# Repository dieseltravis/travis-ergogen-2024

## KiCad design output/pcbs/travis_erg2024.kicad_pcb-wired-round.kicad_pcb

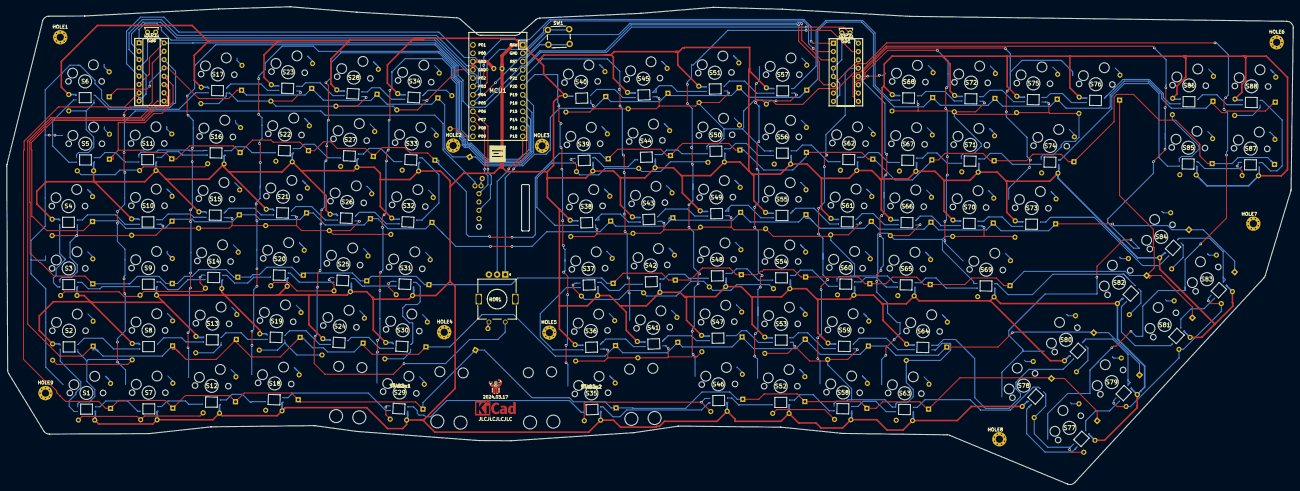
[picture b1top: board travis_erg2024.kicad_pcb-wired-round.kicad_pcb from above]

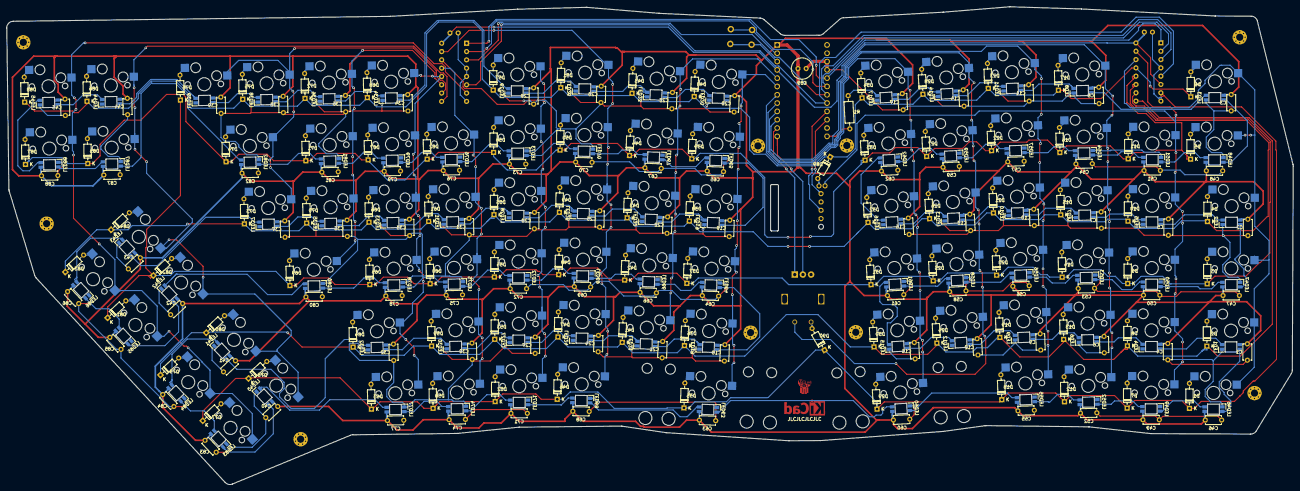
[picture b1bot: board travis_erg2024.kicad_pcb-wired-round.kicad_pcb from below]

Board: 2 copper layers, 393.3 x 146.1 mm, 379 parts (268 on the bottom side), 210 nets.

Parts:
C1, C2, C3, C4, C5, C6, C7, C8, C9, C10, C11, C12, C13, C14, C15, C16, C17, C18, C19, C20, C21, C22, C23, C24, C25, C26, C27, C28, C29, C30, C31, C32, C33, C34, C35, C36, C37, C38, C39, C40, C41, C42, C43, C44, C45, C46, C47, C48, C49, C50, C51, C52, C53, C54, C55, C56, C57, C58, C59, C60, C61, C62, C63, C64, C65, C66, C67, C68, C69, C70, C71, C72, C73, C74, C75, C76, C77, C78, C79, C80, C81, C82, C83, C84, C85, C86, C87, C88: C_Disc_D4.7mm_W2.5mm_P5.00mm
C89: C_Radial_D6.3mm_H11.0mm_P2.50mm
C90, C91: C_Disc_D3.8mm_W2.6mm_P2.50mm
D1, D2, D3, D4, D5, D6, D7, D8, D9, D10, D11, D12, D13, D14, D15, D16, D17, D18, D19, D20, D21, D22, D23, D24, D25, D26, D27, D28, D29, D30, D31, D32, D33, D34, D35, D36, D37, D38, D39, D40, D41, D42, D43, D44, D45, D46, D47, D48, D49, D50, D51, D52, D53, D54, D55, D56, D57, D58, D59, D60, D61, D62, D63, D64, D65, D66, D67, D68, D69, D70, D71, D72, D73, D74, D75, D76, D77, D78, D79, D80, D81, D82, D83, D84, D85, D86, D87, D88, D89, D90: 1N4148; Diode_DO-35
DIP1, DIP2: DIP-16_W7.62mm_Socket
HOLE1, HOLE2, HOLE3, HOLE4, HOLE5, HOLE6, HOLE7, HOLE8, HOLE9: MountingHole_2.2mm_M2_Pad_Via
LED1, LED2, LED3, LED4, LED5, LED6, LED7, LED8, LED9, LED10, LED11, LED12, LED13, LED14, LED15, LED16, LED17, LED18, LED19, LED20, LED21, LED22, LED23, LED24, LED25, LED26, LED27, LED28, LED29, LED30, LED31, LED32, LED33, LED34, LED35, LED36, LED37, LED38, LED39, LED40, LED41, LED42, LED43, LED44, LED45, LED46, LED47, LED48, LED49, LED50, LED51, LED52, LED53, LED54, LED55, LED56, LED57, LED58, LED59, LED60, LED61, LED62, LED63, LED64, LED65, LED66, LED67, LED68, LED69, LED70, LED71, LED72, LED73, LED74, LED75, LED76, LED77, LED78, LED79, LED80, LED81, LED82, LED83, LED84, LED85, LED86, LED87, LED88: led_SK6812mini-e (per-keysingle-side)
LOGO1: ergogen
LOGO2: travis
MCU1: ProMicro
R1: R_Axial_DIN0207_L6.3mm_D2.5mm_P10.16mm_Horizontal
ROT1: rotary_encoder
S1, S2, S3, S4, S5, S6, S7, S8, S9, S10, S11, S12, S13, S14, S15, S16, S17, S18, S19, S20, S21, S22, S23, S24, S25, S26, S27, S28, S29, S30, S31, S32, S33, S34, S35, S36, S37, S38, S39, S40, S41, S42, S43, S44, S45, S46, S47, S48, S49, S50, S51, S52, S53, S54, S55, S56, S57, S58, S59, S60, S61, S62, S63, S64, S65, S66, S67, S68, S69, S70, S71, S72, S73, S74, S75, S76, S77, S78, S79, S80, S81, S82, S83, S84, S85, S86, S87, S88: MX
STAB2u1, STAB2u2: Stabilizer_MX_2.00u
STAB3u1, STAB3u2: Stabilizer_MX_3.00u
SW1: SW_PUSH_6mm_H4.3mm
SYM1: KiCad-Logo_5mm_Copper

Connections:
GND: C1.2, C2.2, C3.2, C4.2, C5.2, C6.2, C7.2, C8.2, C9.2, C10.2, C11.2, C12.2, C13.2, C14.2, C15.2, C16.2, C17.2, C18.2, C19.2, C20.2, C21.2, C22.2, C23.2, C24.2, C25.2, C26.2, C27.2, C28.2, C29.2, C30.2, C31.2, C32.2, C33.2, C34.2, C35.2, C36.2, C37.2, C38.2, C39.2, C40.2, C41.2, C42.2, C43.2, C44.2, C45.2, C46.2, C47.2, C48.2, C49.2, C50.2, C51.2, C52.2, C53.2, C54.2, C55.2, C56.2, C57.2, C58.2, C59.2, C60.2, C61.2, C62.2, C63.2, C64.2, C65.2, C66.2, C67.2, C68.2, C69.2, C70.2, C71.2, C72.2, C73.2, C74.2, C75.2, C76.2, C77.2, C78.2, C79.2, C80.2, C81.2, C82.2, C83.2, C84.2, C85.2, C86.2, C87.2, C88.2, C89.2, C90.2, C91.2, DIP1.4, DIP1.8, DIP2.4, DIP2.5, DIP2.8, LED1.3, LED2.3, LED3.3, LED4.3, LED5.3, LED6.3, LED7.3, LED8.3, LED9.3, LED10.3, LED11.3, LED12.3, LED13.3, LED14.3, LED15.3, LED16.3, LED17.3, LED18.3, LED19.3, LED20.3, LED21.3, LED22.3, LED23.3, LED24.3, LED25.3, LED26.3, LED27.3, LED28.3, LED29.3, LED30.3, LED31.3, LED32.3, LED33.3, LED34.3, LED35.3, LED36.3, LED37.3, LED38.3, LED39.3, LED40.3, LED41.3, LED42.3, LED43.3, LED44.3, LED45.3, LED46.3, LED47.3, LED48.3, LED49.3, LED50.3, LED51.3, LED52.3, LED53.3, LED54.3, LED55.3, LED56.3, LED57.3, LED58.3, LED59.3, LED60.3, LED61.3, LED62.3, LED63.3, LED64.3, LED65.3, LED66.3, LED67.3, LED68.3, LED69.3, LED70.3, LED71.3, LED72.3, LED73.3, LED74.3, LED75.3, LED76.3, LED77.3, LED78.3, LED79.3, LED80.3, LED81.3, LED82.3, LED83.3, LED84.3, LED85.3, LED86.3, LED87.3, LED88.3, MCU1.2, MCU1.15, MCU1.16, ROT1.B, SW1.1
LED: MCU1.24, R1.1
LED_0: LED17.4, R1.2
LED_1: LED14.4, LED17.2
LED_2: LED11.4, LED14.2
LED_3: LED8.4, LED11.2
LED_4: LED3.4, LED8.2
LED_5: LED3.2, LED48.4
LED_6: LED48.2, LED51.4
LED_7: LED51.2, LED54.4
LED_8: LED54.2, LED57.4
LED_9: LED57.2, LED59.4
LED_10: LED59.2, LED62.4
LED_11: LED16.4, LED62.2
LED_12: LED13.4, LED16.2
LED_13: LED10.4, LED13.2
LED_14: LED7.4, LED10.2
LED_15: LED5.4, LED7.2
LED_16: LED2.4, LED5.2
LED_17: LED2.2, LED47.4
LED_18: LED47.2, LED50.4
LED_19: LED50.2, LED53.4
LED_20: LED53.2, LED56.4
LED_21: LED56.2, LED58.4
LED_22: LED58.2, LED61.4
LED_23: LED15.4, LED61.2
LED_24: LED12.4, LED15.2
LED_25: LED9.4, LED12.2
LED_26: LED6.4, LED9.2
LED_27: LED4.4, LED6.2
LED_28: LED1.4, LED4.2
LED_29: LED1.2, LED46.4
LED_30: LED46.2, LED49.4
LED_31: LED49.2, LED52.4
LED_32: LED52.2, LED55.4
LED_33: LED55.2, LED60.4
LED_34: LED60.2, LED63.4
LED_35: LED63.2, LED68.4
LED_36: LED68.2, LED71.4
LED_37: LED71.2, LED74.4
LED_38: LED74.2, LED77.4
LED_39: LED40.4, LED77.2
LED_40: LED40.2, LED83.4
LED_41: LED83.2, LED84.4
LED_42: LED41.4, LED84.2
LED_43: LED32.4, LED41.2
LED_44: LED30.4, LED32.2
LED_45: LED27.4, LED30.2
LED_46: LED24.4, LED27.2
LED_47: LED21.4, LED24.2
LED_48: LED18.4, LED21.2
LED_49: LED18.2, LED64.4
LED_50: LED64.2, LED66.4
LED_51: LED66.2, LED69.4
LED_52: LED69.2, LED72.4
LED_53: LED72.2, LED75.4
LED_54: LED75.2, LED78.4
LED_55: LED78.2, LED80.4
LED_56: LED42.4, LED80.2
LED_57: LED42.2, LED85.4
LED_58: LED85.2, LED86.4
LED_59: LED43.4, LED86.2
LED_60: LED37.4, LED43.2
LED_61: LED35.4, LED37.2
LED_62: LED33.4, LED35.2
LED_63: LED31.4, LED33.2
LED_64: LED28.4, LED31.2
LED_65: LED25.4, LED28.2
LED_66: LED22.4, LED25.2
LED_67: LED19.4, LED22.2
LED_68: LED19.2, LED65.4
LED_69: LED65.2, LED67.4
LED_70: LED67.2, LED70.4
LED_71: LED70.2, LED73.4
LED_72: LED73.2, LED76.4
LED_73: LED76.2, LED79.4
LED_74: LED79.2, LED81.4
LED_75: LED81.2, LED82.4
LED_76: LED82.2, LED87.4
LED_77: LED87.2, LED88.4
LED_78: LED45.4, LED88.2
LED_79: LED44.4, LED45.2
LED_80: LED39.4, LED44.2
LED_81: LED38.4, LED39.2
LED_82: LED36.4, LED38.2
LED_83: LED34.4, LED36.2
LED_84: LED29.4, LED34.2
LED_85: LED26.4, LED29.2
LED_86: LED23.4, LED26.2
LED_87: LED20.4, LED23.2
RAW: C1.1, C2.1, C3.1, C4.1, C5.1, C6.1, C7.1, C8.1, C9.1, C10.1, C11.1, C12.1, C13.1, C14.1, C15.1, C16.1, C17.1, C18.1, C19.1, C20.1, C21.1, C22.1, C23.1, C24.1, C25.1, C26.1, C27.1, C28.1, C29.1, C30.1, C31.1, C32.1, C33.1, C34.1, C35.1, C36.1, C37.1, C38.1, C39.1, C40.1, C41.1, C42.1, C43.1, C44.1, C45.1, C46.1, C47.1, C48.1, C49.1, C50.1, C51.1, C52.1, C53.1, C54.1, C55.1, C56.1, C57.1, C58.1, C59.1, C60.1, C61.1, C62.1, C63.1, C64.1, C65.1, C66.1, C67.1, C68.1, C69.1, C70.1, C71.1, C72.1, C73.1, C74.1, C75.1, C76.1, C77.1, C78.1, C79.1, C80.1, C81.1, C82.1, C83.1, C84.1, C85.1, C86.1, C87.1, C88.1, C89.1, LED1.1, LED2.1, LED3.1, LED4.1, LED5.1, LED6.1, LED7.1, LED8.1, LED9.1, LED10.1, LED11.1, LED12.1, LED13.1, LED14.1, LED15.1, LED16.1, LED17.1, LED18.1, LED19.1, LED20.1, LED21.1, LED22.1, LED23.1, LED24.1, LED25.1, LED26.1, LED27.1, LED28.1, LED29.1, LED30.1, LED31.1, LED32.1, LED33.1, LED34.1, LED35.1, LED36.1, LED37.1, LED38.1, LED39.1, LED40.1, LED41.1, LED42.1, LED43.1, LED44.1, LED45.1, LED46.1, LED47.1, LED48.1, LED49.1, LED50.1, LED51.1, LED52.1, LED53.1, LED54.1, LED55.1, LED56.1, LED57.1, LED58.1, LED59.1, LED60.1, LED61.1, LED62.1, LED63.1, LED64.1, LED65.1, LED66.1, LED67.1, LED68.1, LED69.1, LED70.1, LED71.1, LED72.1, LED73.1, LED74.1, LED75.1, LED76.1, LED77.1, LED78.1, LED79.1, LED80.1, LED81.1, LED82.1, LED83.1, LED84.1, LED85.1, LED86.1, LED87.1, LED88.1, MCU1.1
RST: MCU1.3, SW1.2
VCC: C90.1, C91.1, DIP1.6, DIP1.16, DIP2.16, MCU1.4
arrows_left_bottom: D77.2, S77.2
arrows_left_top: D78.2, S78.2
arrows_right_bottom: D79.2, S79.2
arrows_right_top: D80.2, S80.2
col0: DIP1.14, S1.1, S2.1, S3.1, S4.1, S5.1, S6.1
col1: DIP1.15, S7.1, S8.1, S9.1, S10.1, S11.1
col2: MCU1.10, S12.1, S13.1, S14.1, S15.1, S16.1, S17.1
col3: MCU1.9, S18.1, S19.1, S20.1, S21.1, S22.1, S23.1
col4: MCU1.8, ROT1.1, S24.1, S25.1, S26.1, S27.1, S28.1
col5: MCU1.7, S29.1, S30.1, S31.1, S32.1, S33.1, S34.1
col6: MCU1.6, S35.1, S36.1, S37.1, S38.1, S39.1, S40.1
col7: MCU1.5, S41.1, S42.1, S43.1, S44.1, S45.1
col8: DIP2.15, S46.1, S47.1, S48.1, S49.1, S50.1, S51.1
col9: DIP2.14, S52.1, S53.1, S54.1, S55.1, S56.1, S57.1
col10: DIP2.13, S58.1, S59.1, S60.1, S61.1, S62.1
col11: DIP2.12, S63.1, S64.1, S65.1, S66.1, S67.1, S68.1
col12: DIP2.11, S69.1, S70.1, S71.1, S72.1
col13: DIP2.10, S73.1, S74.1, S75.1, S76.1
col14: DIP2.9, S78.1, S80.1, S82.1, S84.1, S85.1, S86.1
col15: DIP2.7, S77.1, S79.1, S81.1, S83.1, S87.1, S88.1
encA: MCU1.11, ROT1.A
encC: MCU1.12, ROT1.C
enc_to: D90.2, ROT1.2
matrixl_index_bottom: D24.2, S24.2
matrixl_index_func: D28.2, S28.2
matrixl_index_home: D25.2, S25.2
matrixl_index_num: D27.2, S27.2
matrixl_index_top: D26.2, S26.2
matrixl_inner_bottom: D30.2, S30.2
matrixl_inner_func: D34.2, S34.2
matrixl_inner_home: D31.2, S31.2
matrixl_inner_mod: D29.2, S29.2
matrixl_inner_num: D33.2, S33.2
matrixl_inner_top: D32.2, S32.2
matrixl_middle_bottom: D19.2, S19.2
matrixl_middle_func: D23.2, S23.2
matrixl_middle_home: D20.2, S20.2
matrixl_middle_mod: D18.2, S18.2
matrixl_middle_num: D22.2, S22.2
matrixl_middle_top: D21.2, S21.2
matrixl_outer_bottom: D2.2, S2.2
matrixl_outer_func: D6.2, S6.2
matrixl_outer_home: D3.2, S3.2
matrixl_outer_mod: D1.2, S1.2
matrixl_outer_num: D5.2, S5.2
matrixl_outer_top: D4.2, S4.2
matrixl_pinky_bottom: D8.2, S8.2
matrixl_pinky_home: D9.2, S9.2
matrixl_pinky_mod: D7.2, S7.2
matrixl_pinky_num: D11.2, S11.2
matrixl_pinky_top: D10.2, S10.2
matrixl_ring_bottom: D13.2, S13.2
matrixl_ring_func: D17.2, S17.2
matrixl_ring_home: D14.2, S14.2
matrixl_ring_mod: D12.2, S12.2
matrixl_ring_num: D16.2, S16.2
matrixl_ring_top: D15.2, S15.2
matrixr_index_bottom: D41.2, S41.2
matrixr_index_func: D45.2, S45.2
matrixr_index_home: D42.2, S42.2
matrixr_index_num: D44.2, S44.2
matrixr_index_top: D43.2, S43.2
matrixr_inner_bottom: D36.2, S36.2
matrixr_inner_func: D40.2, S40.2
matrixr_inner_home: D37.2, S37.2
matrixr_inner_mod: D35.2, S35.2
matrixr_inner_num: D39.2, S39.2
matrixr_inner_top: D38.2, S38.2
matrixr_middle_bottom: D47.2, S47.2
matrixr_middle_func: D51.2, S51.2
matrixr_middle_home: D48.2, S48.2
matrixr_middle_mod: D46.2, S46.2
matrixr_middle_num: D50.2, S50.2
matrixr_middle_top: D49.2, S49.2
matrixr_outer2_func: D72.2, S72.2
matrixr_outer2_home: D69.2, S69.2
matrixr_outer2_num: D71.2, S71.2
matrixr_outer2_top: D70.2, S70.2
matrixr_outer3_func: D75.2, S75.2
matrixr_outer3_num: D74.2, S74.2
matrixr_outer3_top: D73.2, S73.2
matrixr_outer4_func: D76.2, S76.2
matrixr_outer_bottom: D64.2, S64.2
matrixr_outer_func: D68.2, S68.2
matrixr_outer_home: D65.2, S65.2
matrixr_outer_mod: D63.2, S63.2
matrixr_outer_num: D67.2, S67.2
matrixr_outer_top: D66.2, S66.2
matrixr_pinky_bottom: D59.2, S59.2
matrixr_pinky_home: D60.2, S60.2
matrixr_pinky_mod: D58.2, S58.2
matrixr_pinky_num: D62.2, S62.2
matrixr_pinky_top: D61.2, S61.2
matrixr_ring_bottom: D53.2, S53.2
matrixr_ring_func: D57.2, S57.2
matrixr_ring_home: D54.2, S54.2
matrixr_ring_mod: D52.2, S52.2
matrixr_ring_num: D56.2, S56.2
matrixr_ring_top: D55.2, S55.2
mux0: DIP1.1, DIP2.1, MCU1.17
mux1: DIP1.2, DIP2.2, MCU1.18
mux2: DIP1.3, DIP2.3, MCU1.19
mux3: DIP1.5, DIP2.6, MCU1.20
pages_left_bottom: D81.2, S81.2
pages_left_top: D82.2, S82.2
pages_right_bottom: D83.2, S83.2
pages_right_top: D84.2, S84.2
row0: D6.1, D17.1, D23.1, D28.1, D34.1, D40.1, D45.1, D51.1, D57.1, D68.1, D72.1, D75.1, D86.1, D88.1, D89.1, DIP1.13
row1: D5.1, D11.1, D16.1, D22.1, D27.1, D33.1, D39.1, D44.1, D50.1, D56.1, D62.1, D67.1, D71.1, D74.1, D85.1, D87.1, DIP1.12
row2: D4.1, D10.1, D15.1, D21.1, D26.1, D32.1, D38.1, D43.1, D49.1, D55.1, D61.1, D66.1, D70.1, D73.1, D83.1, D84.1, DIP1.11
row3: D3.1, D9.1, D14.1, D20.1, D25.1, D31.1, D37.1, D42.1, D48.1, D54.1, D60.1, D65.1, D69.1, D76.1, D81.1, D82.1, DIP1.10
row4: D2.1, D8.1, D13.1, D19.1, D24.1, D30.1, D36.1, D41.1, D47.1, D53.1, D59.1, D64.1, D79.1, D80.1, DIP1.9
row5: D1.1, D7.1, D12.1, D18.1, D29.1, D35.1, D46.1, D52.1, D58.1, D63.1, D77.1, D78.1, D90.1, DIP1.7
special_left_bottom: D85.2, S85.2
special_left_top: D86.2, S86.2
special_right_bottom: D87.2, S87.2
special_right_top: D88.2, S88.2

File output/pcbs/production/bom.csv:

Designator,Footprint,Quantity,Value,LCSC Part #
C1,C_Radial_D6.3mm_H11.0mm_P2.50mm,1,C_Radial_D6.3mm_H11.0mm_P2.50mm,
"C2, C3",C_Disc_D3.8mm_W2.6mm_P2.50mm,2,C_Disc_D3.8mm_W2.6mm_P2.50mm,
"D1, D2, KD1, KD10, KD11, KD12, KD13, KD14, KD15, KD16, KD17, KD18, KD19, KD2, KD20, KD21, KD22, KD23, KD24, KD25, KD26, KD27, KD28, KD29, KD3, KD30, KD31, KD32, KD33, KD34, KD35, KD36, KD37, KD38, KD39, KD4, KD40, KD41, KD42, KD43, KD44, KD45, KD46, KD47, KD48, KD49, KD5, KD50, KD51, KD52, KD53, KD54, KD55, KD56, KD57, KD58, KD59, KD6, KD60, KD61, KD62, KD63, KD64, KD65, KD66, KD67, KD68, KD69, KD7, KD70, KD71, KD72, KD73, KD74, KD75, KD76, KD77, KD78, KD79, KD8, KD80, KD81, KD82, KD83, KD84, KD85, KD86, KD87, KD88, KD9",Diode_DO-35,90,1N4148,
"DIP1, DIP2",DIP-16_W7.62mm_Socket,2,DIP-16_W7.62mm_Socket,
"HOLE1, HOLE2, HOLE3, HOLE4, HOLE5, HOLE6, HOLE7, HOLE8, HOLE9",MountingHole_2.2mm_M2_Pad_Via,9,,
"KC1, KC10, KC11, KC12, KC13, KC14, KC15, KC16, KC17, KC18, KC19, KC2, KC20, KC21, KC22, KC23, KC24, KC25, KC26, KC27, KC28, KC29, KC3, KC30, KC31, KC32, KC33, KC34, KC35, KC36, KC37, KC38, KC39, KC4, KC40, KC41, KC42, KC43, KC44, KC45, KC46, KC47, KC48, KC49, KC5, KC50, KC51, KC52, KC53, KC54, KC55, KC56, KC57, KC58, KC59, KC6, KC60, KC61, KC62, KC63, KC64, KC65, KC66, KC67, KC68, KC69, KC7, KC70, KC71, KC72, KC73, KC74, KC75, KC76, KC77, KC78, KC79, KC8, KC80, KC81, KC82, KC83, KC84, KC85, KC86, KC87, KC88, KC9",C_Disc_D4.7mm_W2.5mm_P5.00mm,88,104,
"KLED1, KLED10, KLED11, KLED12, KLED13, KLED14, KLED15, KLED16, KLED17, KLED18, KLED19, KLED2, KLED20, KLED21, KLED22, KLED23, KLED24, KLED25, KLED26, KLED27, KLED28, KLED29, KLED3, KLED30, KLED31, KLED32, KLED33, KLED34, KLED35, KLED36, KLED37, KLED38, KLED39, KLED4, KLED40, KLED41, KLED42, KLED43, KLED44, KLED45, KLED46, KLED47, KLED48, KLED49, KLED5, KLED50, KLED51, KLED52, KLED53, KLED54, KLED55, KLED56, KLED57, KLED58, KLED59, KLED6, KLED60, KLED61, KLED62, KLED63, KLED64, KLED65, KLED66, KLED67, KLED68, KLED69, KLED7, KLED70, KLED71, KLED72, KLED73, KLED74, KLED75, KLED76, KLED77, KLED78, KLED79, KLED8, KLED80, KLED81, KLED82, KLED83, KLED84, KLED85, KLED86, KLED87, KLED88, KLED9",led_SK6812mini-e (per-key single-side),88,SK6812mini-e,
"KSW1, KSW10, KSW11, KSW12, KSW13, KSW14, KSW15, KSW16, KSW17, KSW18, KSW19, KSW2, KSW20, KSW21, KSW22, KSW23, KSW24, KSW25, KSW26, KSW27, KSW28, KSW29, KSW3, KSW30, KSW31, KSW32, KSW33, KSW34, KSW35, KSW36, KSW37, KSW38, KSW39, KSW4, KSW40, KSW41, KSW42, KSW43, KSW44, KSW45, KSW46, KSW47, KSW48, KSW49, KSW5, KSW50, KSW51, KSW52, KSW53, KSW54, KSW55, KSW56, KSW57, KSW58, KSW59, KSW6, KSW60, KSW61, KSW62, KSW63, KSW64, KSW65, KSW66, KSW67, KSW68, KSW69, KSW7, KSW70, KSW71, KSW72, KSW73, KSW74, KSW75, KSW76, KSW77, KSW78, KSW79, KSW8, KSW80, KSW81, KSW82, KSW83, KSW84, KSW85, KSW86, KSW87, KSW88, KSW9",MX,88,Kailh MX Switch Sockets,
MCU1,ProMicro,1,,
R1,R_Axial_DIN0207_L6.3mm_D2.5mm_P10.16mm_Horizontal,1,R_Axial_DIN0207_L6.3mm_D2.5mm_P10.16mm_Horizontal,
ROT1,rotary_encoder,1,,
SW1,SW_PUSH_6mm_H4.3mm,1,SW_PUSH_6mm_H4.3mm,

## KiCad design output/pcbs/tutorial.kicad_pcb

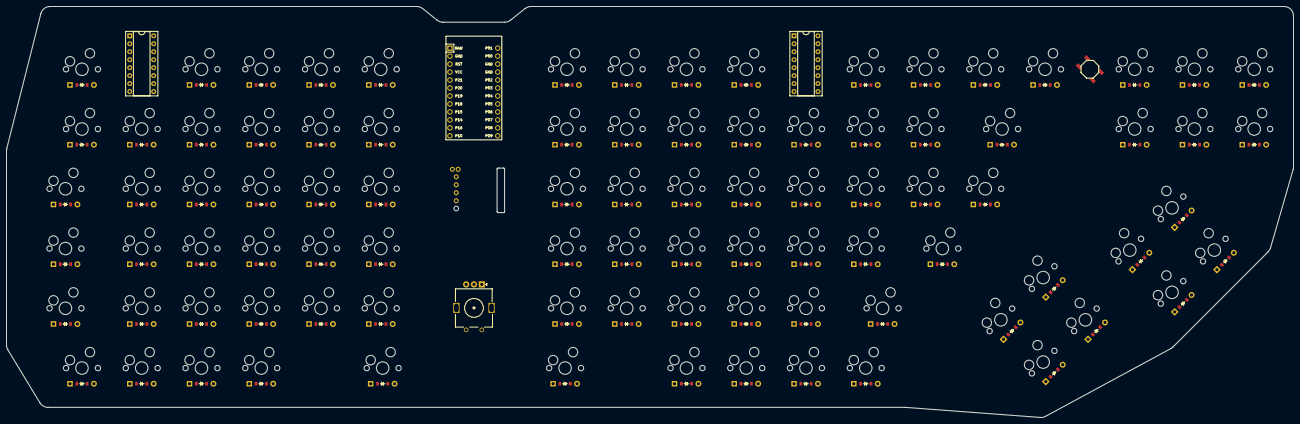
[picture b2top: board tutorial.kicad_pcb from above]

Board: 2 copper layers, 410.2 x 131.0 mm, 185 parts (0 on the bottom side), 52 nets, no tracks yet.

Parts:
B1: SW_TACT_ALPS_SKQGABE010
D1, D2, D3, D4, D5, D6, D7, D8, D9, D10, D11, D12, D13, D14, D15, D16, D17, D18, D19, D20, D21, D22, D23, D24, D25, D26, D27, D28, D29, D30, D31, D32, D33, D34, D35, D36, D37, D38, D39, D40, D41, D42, D43, D44, D45, D46, D47, D48, D49, D50, D51, D52, D53, D54, D55, D56, D57, D58, D59, D60, D61, D62, D63, D64, D65, D66, D67, D68, D69, D70, D71, D72, D73, D74, D75, D76, D77, D78, D79, D80, D81, D82, D83, D84, D85, D86, D87, D88, D89, D90: ComboDiode
DIP1, DIP2: DIP-16_W7.62mm_Socket
MCU1: ProMicro
ROT1: rotary_encoder
S1, S2, S3, S4, S5, S6, S7, S8, S9, S10, S11, S12, S13, S14, S15, S16, S17, S18, S19, S20, S21, S22, S23, S24, S25, S26, S27, S28, S29, S30, S31, S32, S33, S34, S35, S36, S37, S38, S39, S40, S41, S42, S43, S44, S45, S46, S47, S48, S49, S50, S51, S52, S53, S54, S55, S56, S57, S58, S59, S60, S61, S62, S63, S64, S65, S66, S67, S68, S69, S70, S71, S72, S73, S74, S75, S76, S77, S78, S79, S80, S81, S82, S83, S84, S85, S86, S87, S88, S89, S90: MX

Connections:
GND: B1.1, DIP1.1, DIP1.2, DIP1.3, DIP1.4, DIP1.5, DIP1.6, DIP1.7, DIP1.8, DIP1.9, DIP1.10, DIP1.11, DIP1.12, DIP1.13, DIP1.14, DIP1.15, DIP2.1, DIP2.2, DIP2.3, DIP2.4, DIP2.5, DIP2.6, DIP2.7, DIP2.8, DIP2.9, DIP2.10, DIP2.11, DIP2.12, DIP2.13, DIP2.14, DIP2.15, MCU1.2, MCU1.15, MCU1.16, ROT1.1, ROT1.2, ROT1.A, ROT1.B, ROT1.C
RST: B1.2, MCU1.3
VCC: DIP1.16, DIP2.16, MCU1.4
index_bottom: D25.2, D41.2, S25.2, S41.2
index_func: D29.2, D45.2, S29.2, S45.2
index_home: D26.2, D42.2, S26.2, S42.2
index_mod: D24.2, S24.2
index_num: D28.2, D44.2, S28.2, S44.2
index_top: D27.2, D43.2, S27.2, S43.2
inner_bottom: D30.2, D36.2, S30.2, S36.2
inner_func: D34.2, D40.2, S34.2, S40.2
inner_home: D31.2, D37.2, S31.2, S37.2
inner_mod: D35.2, S35.2
inner_num: D33.2, D39.2, S33.2, S39.2
inner_top: D32.2, D38.2, S32.2, S38.2
left_bottom: D77.2, D81.2, D85.2, S77.2, S81.2, S85.2
left_top: D78.2, D82.2, D86.2, S78.2, S82.2, S86.2
mid_bottom: D87.2, S87.2
mid_top: D88.2, S88.2
middle_bottom: D19.2, D47.2, S19.2, S47.2
middle_func: D23.2, D51.2, S23.2, S51.2
middle_home: D20.2, D48.2, S20.2, S48.2
middle_mod: D18.2, D46.2, S18.2, S46.2
middle_num: D22.2, D50.2, S22.2, S50.2
middle_top: D21.2, D49.2, S21.2, S49.2
outer2_func: D72.2, S72.2
outer2_home: D69.2, S69.2
outer2_num: D71.2, S71.2
outer2_top: D70.2, S70.2
outer3_func: D75.2, S75.2
outer3_num: D74.2, S74.2
outer3_top: D73.2, S73.2
outer4_func: D76.2, S76.2
outer_bottom: D2.2, D64.2, S2.2, S64.2
outer_func: D6.2, D68.2, S6.2, S68.2
outer_home: D3.2, D65.2, S3.2, S65.2
outer_mod: D1.2, D63.2, S1.2, S63.2
outer_num: D5.2, D67.2, S5.2, S67.2
outer_top: D4.2, D66.2, S4.2, S66.2
pinky_bottom: D8.2, D59.2, S8.2, S59.2
pinky_home: D9.2, D60.2, S9.2, S60.2
pinky_mod: D7.2, D58.2, S7.2, S58.2
pinky_num: D11.2, D62.2, S11.2, S62.2
pinky_top: D10.2, D61.2, S10.2, S61.2
right_bottom: D79.2, D83.2, D89.2, S79.2, S83.2, S89.2
right_top: D80.2, D84.2, D90.2, S80.2, S84.2, S90.2
ring_bottom: D13.2, D53.2, S13.2, S53.2
ring_func: D17.2, D57.2, S17.2, S57.2
ring_home: D14.2, D54.2, S14.2, S54.2
ring_mod: D12.2, D52.2, S12.2, S52.2
ring_num: D16.2, D56.2, S16.2, S56.2
ring_top: D15.2, D55.2, S15.2, S55.2
